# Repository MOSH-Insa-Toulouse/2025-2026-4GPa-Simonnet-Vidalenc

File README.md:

# Projet Capteur Low-Cost 4A Génie Physique - Max Simonnet & Basile Vidalenc

## Sommaire
- [Projet Capteur Low-Cost 4A Génie Physique - Max Simonnet \& Basile Vidalenc](#projet-capteur-low-cost-4a-génie-physique---max-simonnet--basile-vidalenc)
  - [Sommaire](#sommaire)
  - [1. Description du projet ](#1-description-du-projet-)
    - [1.1 Caractéristiques et travaux de recherche préliminaires sur le capteur ](#11-caractéristiques-et-travaux-de-recherche-préliminaires-sur-le-capteur-)
    - [1.2 Cours et formation ](#12-cours-et-formation-)
  - [2. Livrables du projet ](#2-livrables-du-projet-)
  - [3. Carte Arduino UNO et code associé ](#3-carte-arduino-uno-et-code-associé-)
  - [4. KiCad ](#4-kicad-)
    - [4.1. Symboles et empreintes des composants ](#41-symboles-et-empreintes-des-composants-)
    - [4.2. Schématique ](#42-schématique-)
    - [4.3. Placement des composants ](#43-placement-des-composants-)
  - [5. Fabrication du shield ](#5-fabrication-du-shield-)
    - [5.1 Réalisation du PCB ](#51-réalisation-du-pcb-)
    - [5.2 Perçage et soudure ](#52-perçage-et-soudure-)
  - [6. Logiciel de simulation LTSpice ](#6-logiciel-de-simulation-ltspice-)
  - [8. Tests et résultats ](#8-tests-et-résultats-)
    - [8.1 Banc de test ](#81-banc-de-test-)
    - [8.2 Résultats obtenus et analyses ](#82-résultats-obtenus-et-analyses-)
    - [8.3 Regard critique sur les résultats ](#83-regard-critique-sur-les-résultats-)
  - [9. Datasheet ](#9-datasheet-)

## 1. Description du projet 

Ce projet s'inscrit dans le cadre de l'unité de formation "Du capteur au banc de test en open source hardware". Ce cours est dispensé en quatrième année au sein du département de Génie Physique de l'INSA Toulouse et a pour but de nous sensibiliser aux différentes étapes de conception et d'analyse utiles à la création d'un capteur.

### 1.1 Caractéristiques et travaux de recherche préliminaires sur le capteur 

Le KTY2000 est un exemple de technologie low-tech à base de graphite. Ce projet s’inspire du travail mené par plusieurs scientifiques et publié dans [cet article](https://www.nature.com/articles/srep03812) en 2014. En effet, les études ont révélé les nombreux avantages du carbone graphite. L’électronique à base de papier attire de plus en plus les ingénieur.es de par sa facilité d’approvisionnement, de fabrication et son faible coût. Il suffit dans notre cas de déposer une fine couche de graphite sur le substrat naturellement poreux pour former la base du capteur. Les mines de crayon sont constituées de réseaux percolés de fines poudres de graphite liées entre elles par des argiles, permettant d’obtenir après dépôt de fins films conducteurs non fabriqués en laboratoire. 

Le système à l’étude est granulaire, autrement dit il existe une dépendance entre la conductivité électrique (notamment par effet tunnel) et l’espace moyen entre les nanoparticules de graphite. Ainsi, une déformation de la feuille de papier va modifier la conductivité globale de la couche de graphite, induisant des changements de résistances réversibles lors des déformations en compression ou en traction. Ceci constitue en fait le principe d'une jauge de contrainte. 
L’expérience est réalisée avec différentes duretés de mine de crayon (2H, HB, 2B). Les mesures de résistance pour chaque crayon sont réalisées en fonction de différents rayons de courbure (soit la déformation) ou de l’angle de flexion de notre capteur. Cela permet une caractérisation complète de chaque type de crayon et ainsi de notre capteur. 

Dans notre cas, les traces de crayon sont déposées sur du papier comme vu ci-dessous. Une fois colorié, le capteur est connecté à un système de mesures externe via des pinces crocodiles reliées à un PCB et branché sur une carte Arduino Uno.

<p align="center">

### 1.2 Cours et formation 

Pour mener ce projet, nous avons d'abord suivi différents cours et TPs.
- Introduction à la chaîne de mesure
- TP développement d'un capteur à jauge de contrainte à base de crayon graphite
- TP conception d'un circuit analogique pour interfacer le capteur à jauge de contrainte
- TP programmation de microcontrôleurs et développement d'un matériel open source
- TP LTSpice afin de simuler le fonctionnement du circuit électronique comprenant la jauge de contrainte
- TP shield électronique PCB dédié à l'interface du capteur de contrainte
- TP réalisation du banc de test de la jauge de contrainte
- Cours fiche technique de la jauge de contrainte
- Cours Github

<p align="center">

## 2. Livrables du projet 

* Un shield PCB devra être designé et fabriqué. Il sera ensuite connecté à une plaque Arduino UNO. Le shield doit contenir au minimum un amplificateur transimpédence, un module Bluetooth, un écran OLED et un encodeur rotatoire pour la calibration du capteur.

* La carte Arduino fonctionnera avec un code permettant de mesurer la containte appliquée sur le capteur. La carte devra aussi communiquer avec le module Bluetooth, et contrôler et communiquer avec l'écran OLED grâce à l'encodeur rotatoire.

* Une application Android APK
* Un protocole de test
* La datasheet du capteur de contrainte

## 3. Carte Arduino UNO et code associé 

Le code Arduino est consultable [ici]().
Ce code permet la réception des mesures faites par les deux capteurs, la conversion résistance-angle du flex-sensor et celle tension-résistance pour le KTY2000, la gestion de l'affichage sur l'écran OLED et l'envoi de données via un port série.

## 4. KiCad 

Voici la liste des différents composants présents sur notre PCB :

- _x2 résistance 100kΩ_
- _x1 résistance 47kΩ_
- _x1 résistance 10kΩ_
- _x1 résistance 1kΩ_
- _x1 résistance variable MCP41010_
- _x1 capacité 1μF_
- _x2 capacité 100nF_
- _x1 amplificateur opérationnel LTC1050_
- _x1 écran OLED I2C 1306_
- _x1 encodeur rotatoire_
- _x1 servo-moteur_
- _x1 capteur graphite_

### 4.1. Symboles et empreintes des composants 
 
* Amplificateur LTC1050
* MCP41010
* Ecran OLED
* Flex sensor
* Bluetooth HC-05

### 4.2. Schématique 
 
<p align="center">

* Amplificateur LTC1050

* MCP41010

* Ecran OLED

* Flex sensor

* Bluetooth HC-05

### 4.3. Placement des composants 
 
<p align="center">

## 5. Fabrication du shield 
 
### 5.1 Réalisation du PCB 

Le PCB a été fabriqué grâce au matériel mis à disposition au Génie Physique et au Génie Électrique et Informatique de l'INSA Toulouse. Les manipulations ont été faites avec l'aide de Catherine Crouzet. La modélisation du PCB fait sur [KiCad]() a été imprimée sur du papier calque tranparent. Ce motif a été ensuite transféré par UVs sur la plaquette d'epoxy finement recouverte d'une couche de cuivre. À l'aide d'un révelateur, la partie non insolée de la résine a été retirée. La plaquette d'expoxy a été ensuite placée dans un bain de perchlorure de fer pour que le cuivre non protégé par la résine soit retiré de la plaquette. Enfin, la plaque a été nettoyée des dernières traces de résine avec de l'acétone.

Par soucis de convention, les pattes "1" de chaque composant sont en forme de carré

### 5.2 Perçage et soudure 

⌀ 1.0mm : Broches de connexion de la carte Arduino Uno

⌀ 0.8mm : Circuit intérieur du PCB 

## 6. Logiciel de simulation LTSpice 
 
L'ensemble de notre circuit électronique a été simulé sur le logiciel LTSpice afin de comprendre et d'analyser son comportement dans des conditions réelles de valeurs de tension. Les différentes simulations ont permis d'une part de vérifier le bon fonctionnement du circuit et de chacun des composants intégrés, et d'autre part de comprendre l'utilité de chacun. Les images ci-dessous représentent la schématique du circuit. Se référer à la [datasheet] pour de plus amples informations.

## 8. Tests et résultats 

Setup d'utilisation du KTY2000.

### 8.1 Banc de test 

### 8.2 Résultats obtenus et analyses 

Les deux graphes suivant représentent la variation de la résistance relative (en %) en fonction de la déformation appliquée - compression et traction.

Les mines les plus tendres contiennent une proportion plus élevée de particules de graphite. C’est donc pour cette raison que les traces de ce type de crayon paraissent plus foncées sur le papier. À l’inverse, les mines les plus dures contiennent beaucoup de liants argileux et apparaissent plus claires. Cela explique également que les résistances de mines de crayon les plus tendres sont plus faibles que les mines de crayon les plus dures. En effet, sous la traction, les particules de graphite sont davantage écartées les unes des autres favorisant la déconnexion des voies de conduction : le courant est donc minime, la résistance quant à elle augmente.  Sous compression, les particules de graphite contenues dans la trace de crayon se rapprochent, facilitant la conduction du courant à travers le réseau de percolation : la résistance s’abaisse naturellement.

Cette caractéristique est illustrée à travers la variation relative de résistance en fonction de la déformation du capteur. En effet, un crayon qui contient moins de particules de graphite comme le 2H dépose naturellement moins de graphite sur le substrat. Les variations de résistance sont donc plus significatives comme beaucoup de chemins de percolations sont créés ou rompus contrairement au 2B où les déformations n’induisent que de faibles variations relatives de résistance.
 
Il est également notable que le comportement en compression du flex-sensor se rapproche de celui du KTY2000. Nous pouvons en conclure que notre capteur graphite présente des similarités de fonctionnnement qu'un capteur industriel. **Cela confirme l'idée que le low-tech est une alternative pertinente pour le futur de l'industrie.**

### 8.3 Regard critique sur les résultats 
 
Il est important de souligner la variabilité des conditions expérimentales. Entre chaque relevé de points et malgré le fait que les pinces crocodiles sans dents étaient bien fixées, il se peut que l’attache du capteur ait bougée. Les résultats sont imprécis et pour certains discutables au vu de la qualité du montage mais suivent tout de même les lois physiques. 

Nous pourrions amener plusieurs pistes d'améliorations à notre projet :

- Améliorer notre banc de test afin de garantir des résultats optimaux mais surtout pour augmenter sa durée de vie et sa résistance. Par exemple, nous pourrions concevoir de le fabriquer par l'intermédiaire d'une imprimante 3D. 

- Améliorer le setup expérimental en commençant par l'ergonomie de notre PCB afin de le rendre plus fonctionnel pour la réalisation des mesures de résistance. Penser à un meilleur emplacement pour les différents composants, à un système d'accroche pour l'écran OLED, mais aussi pour les pinces crocodile dans le but de limiter le plus possible la variabilité des conditions expérimentales. 

## 9. Datasheet 
 
La datasheet du KTY2000 est consultable [ici]. Elle reprend tous les concepts physiques ainsi que les résultats de mesures et leur analyse. D'autres courbes illustrant la variation de résistance en fonction de l'angle de flexion y figurent, venant compléter les affirmations énoncées tout au long de ce rendu.

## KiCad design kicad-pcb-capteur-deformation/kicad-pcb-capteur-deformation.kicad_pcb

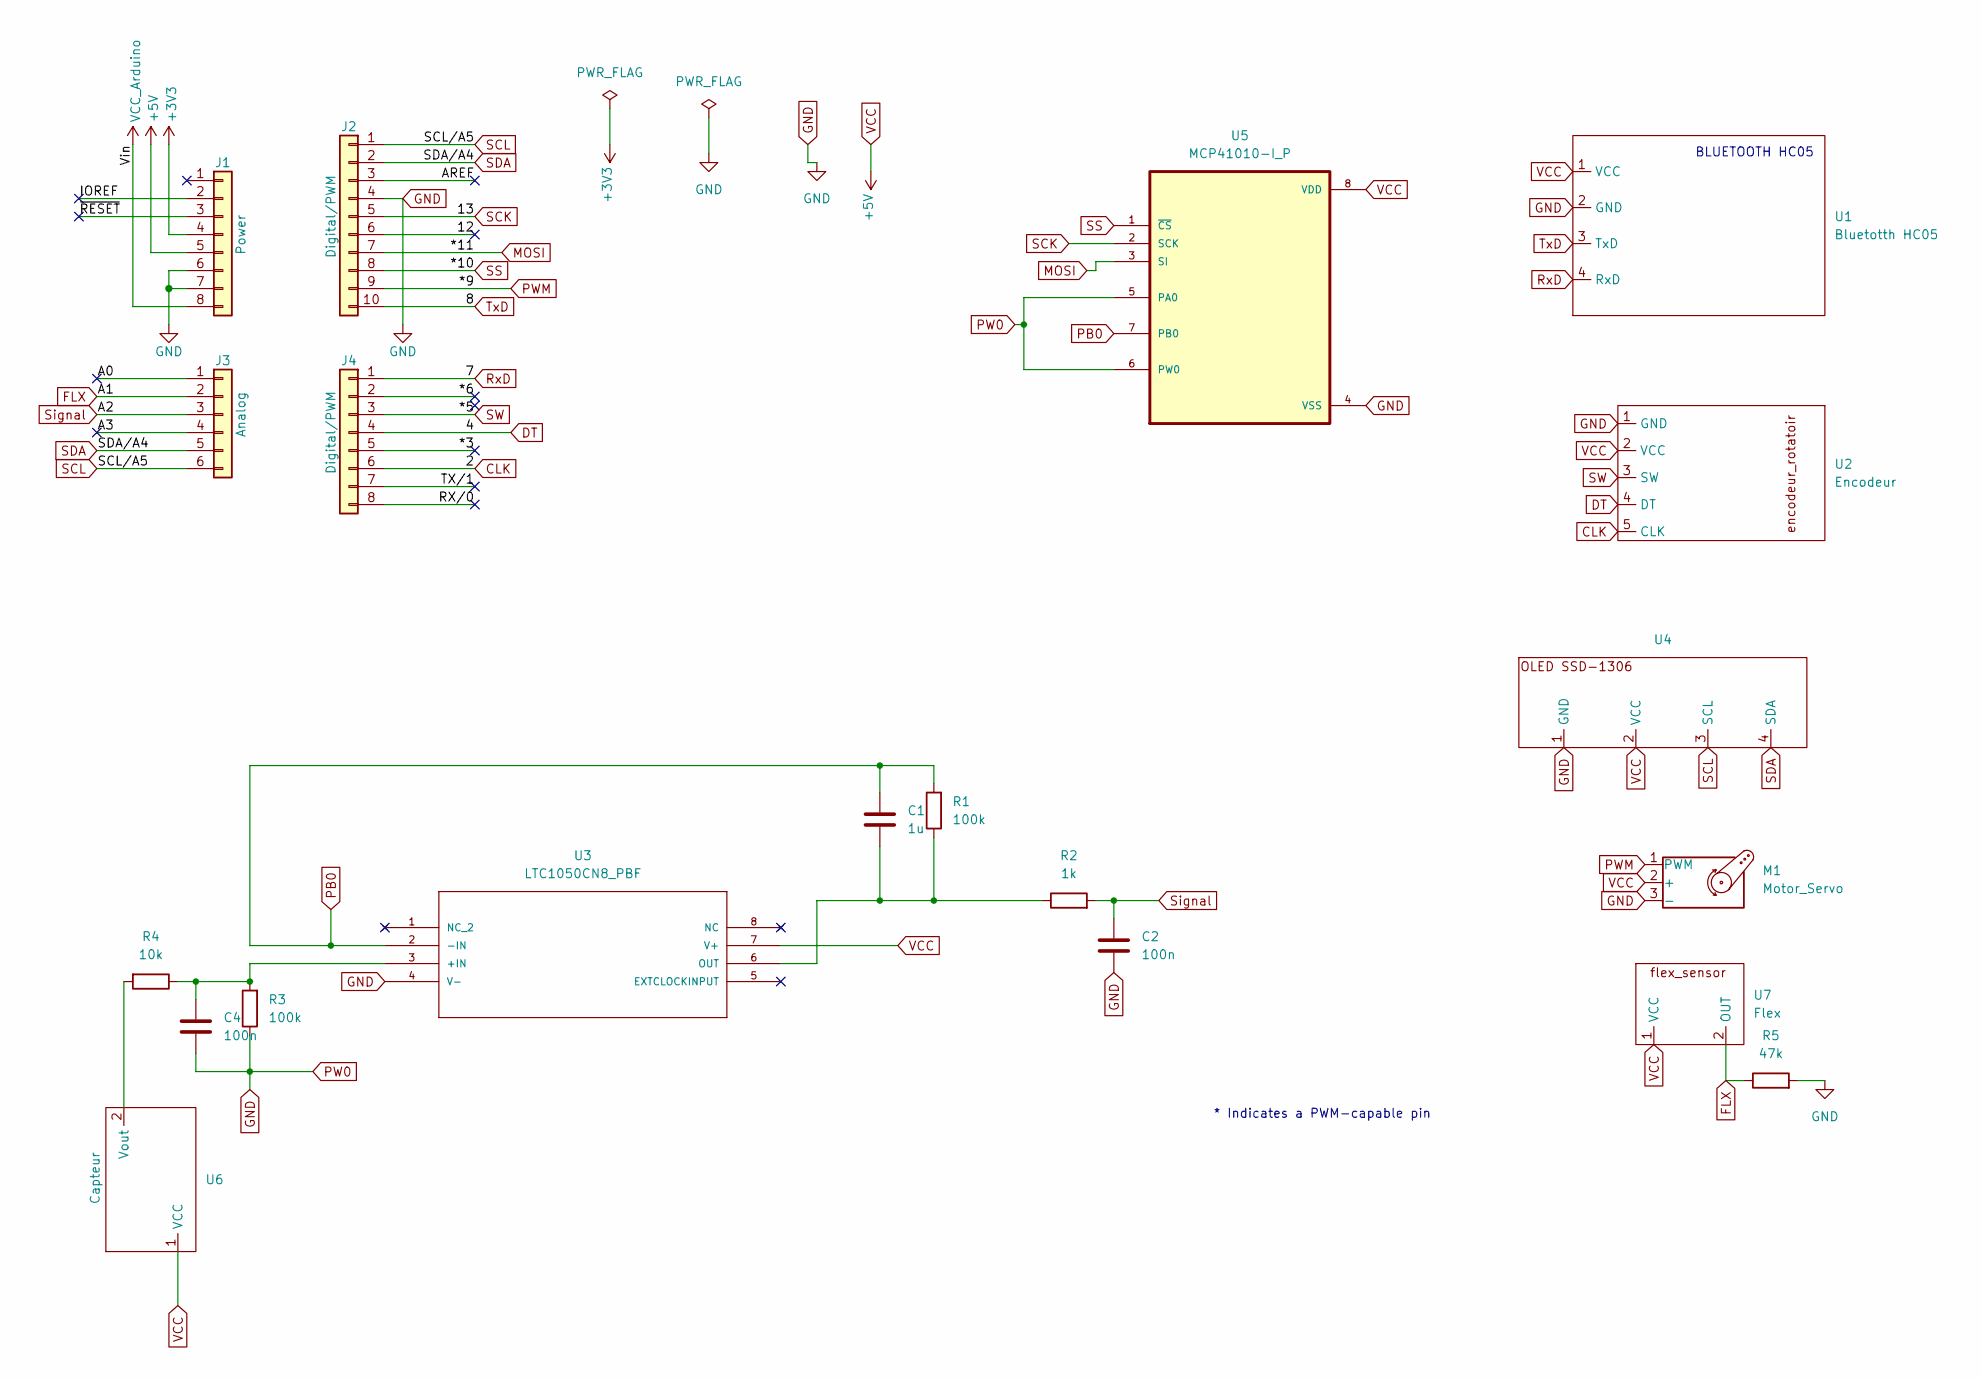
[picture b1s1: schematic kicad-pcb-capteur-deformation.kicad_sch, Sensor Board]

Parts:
C1: 1u; C - 5,08
C2, C4: 100n; C
J1: Power; PinSocket_1x08_P2.54mm_Vertical
J2: Digital/PWM; PinSocket_1x10_P2.54mm_Vertical
J3: Analog; PinSocket_1x06_P2.54mm_Vertical
J4: Digital/PWM; PinSocket_1x08_P2.54mm_Vertical
M1: Motor_Servo; Servo Moteur
R1, R3: 100k; R
R2: 1k; R
R4: 10k; R
R5: 47k; R
U1: Bluetotth HC05; Bluetooth HC05
U2: Encodeur; encodeur_rotatoire
U3: LTC1050CN8_PBF; LTC-1050; MANUFACTURER_PART_NUMBER ltc1050cn8
U4: OLED SSD1306
U5: MCP41010-I_P; Resistance Variable
U6: Capteur
U7: Flex; Flex Sensor

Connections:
+3V3: J1.4
/12: J2.6
/*3: J4.5
/*6: J4.2
/A0: J3.1
/A3: J3.4
/AREF: J2.3
/IOREF: J1.2
/RX/0: J4.8
/TX/1: J4.7
/~RESET: J1.3
CLK: J4.6, U2.5 (CLK)
DT: J4.4, U2.4 (DT)
FLX: J3.2, R5.1, U7.2 (OUT)
GND: C2.2, C4.2, J1.6, J1.7, J2.4, M1.3 (-), R3.1, R5.2, U1.2 (GND), U2.1 (GND), U3.4 (V-), U4.1 (GND), U5.4 (VSS), U5.5 (PA0), U5.6 (PW0)
MOSI: J2.7, U5.3 (SI)
unnamed: C4.1, R3.2, R4.1, U3.3 (+IN)
unnamed: C1.2, R1.1, R2.1, U3.6 (OUT)
unnamed: R4.2, U6.2 (Vout)
PB0: C1.1, R1.2, U3.2 (-IN), U5.7 (PB0)
PWM: J2.9, M1.1 (PWM)
RxD: J4.1, U1.4 (RxD)
SCK: J2.5, U5.2 (SCK)
SCL: J2.1, J3.6, U4.3 (SCL)
SDA: J2.2, J3.5, U4.4 (SDA)
SS: J2.8, U5.1 (~CS)
SW: J4.3, U2.3 (SW)
Signal: C2.1, J3.3, R2.2
TxD: J2.10, U1.3 (TxD)
VCC: J1.5, M1.2 (+), U1.1 (VCC), U2.2 (VCC), U3.7 (V+), U4.2 (VCC), U5.8 (VDD), U6.1 (VCC), U7.1 (VCC)
VCC_Arduino: J1.8

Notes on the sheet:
* Indicates a PWM-capable pin
BLUETOOTH HC05

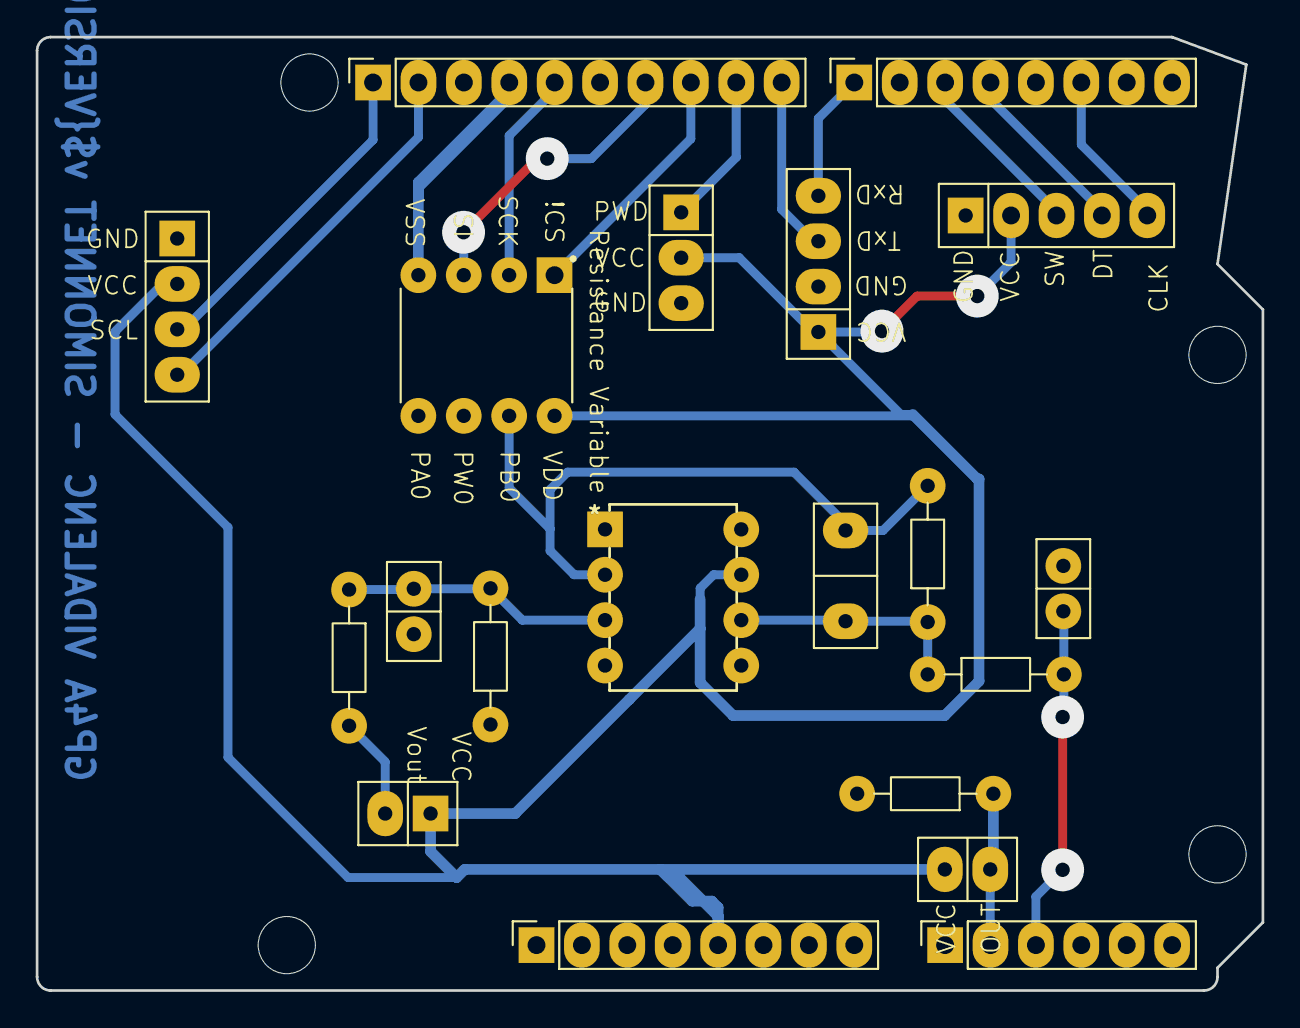
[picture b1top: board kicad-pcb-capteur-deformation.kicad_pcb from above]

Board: 2 copper layers, 68.6 x 53.3 mm, 24 parts (0 on the bottom side), 19 nets.

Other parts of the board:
MH1, MH2, MH3, MH4: MountingHole_3.2mm

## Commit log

2026-02-11 premiers symboles et construction du pcb
2026-02-18 empreintes et début de wiring KiCad
2026-02-18 ignorer les maj des fichiers KiCad
2026-02-18 PCB fini
2026-03-03 maj des fichiers KiCad, VF préliminaire
2026-03-03 maj README
2026-03-03 dossier Arduino et maj README
2026-03-03 complété dossier Images et 3D Models sur KiCad
2026-04-08 ajout d'images
2026-04-08 ajout readme
2026-04-08 tests images sur readme
2026-04-08 test alignement images readme
2026-04-08 test alignement 2
2026-04-08 ajout schéma global
2026-04-08 ajout images dans readme
2026-04-10 Resultats du capteur graphite
2026-04-13 ajout du main.ino et calibration_R2.ino
2026-04-13 ajout datasheet
2026-04-17 ajout app APK

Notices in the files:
parts and their libraries:
COPYRIGHT: Copyright C 2016 Accelerated Designs. All rights reserved
